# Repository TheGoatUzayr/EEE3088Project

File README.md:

# EEE3088F Design Project – Power Subsystem

This repository contains the development files for our **EEE3088F Design Project**, part of the third-year Electrical & Computer Engineering curriculum at the University of Cape Town.

## 🔧 Project Overview

The broader project is the design and implementation of a **multi-disciplinary embedded system**—a micromouse robot capable of navigating a maze autonomously. The system integrates several subsystems, including:

- 🔋 Power  
- 📡 Sensing  
- 🧠 Processing  

Our team focused on the **power subsystem**, which serves as the electrical backbone of the micromouse.

## ⚡ Power Subsystem Objectives

- Deliver stable and sufficient power to all micromouse subsystems  
- Integrate a safe and efficient **LiPo battery charging** mechanism  
- Include **battery monitoring** to track voltage levels  
- Implement a **low-power idle mode** via a physical switch  
- Ensure seamless integration with the sensing and processing units  

## 📁 Repository Structure

- `README.md` – Project overview and repo guide  
- `simulation/` – Top-level development folder  
  - `pcbdesign1/` – Circuit designs, layouts, and BOM

## 👨‍🔬 Contributors
- Uzayr Ballim – Power subsystem
- Kamil Singh – Power subsystem

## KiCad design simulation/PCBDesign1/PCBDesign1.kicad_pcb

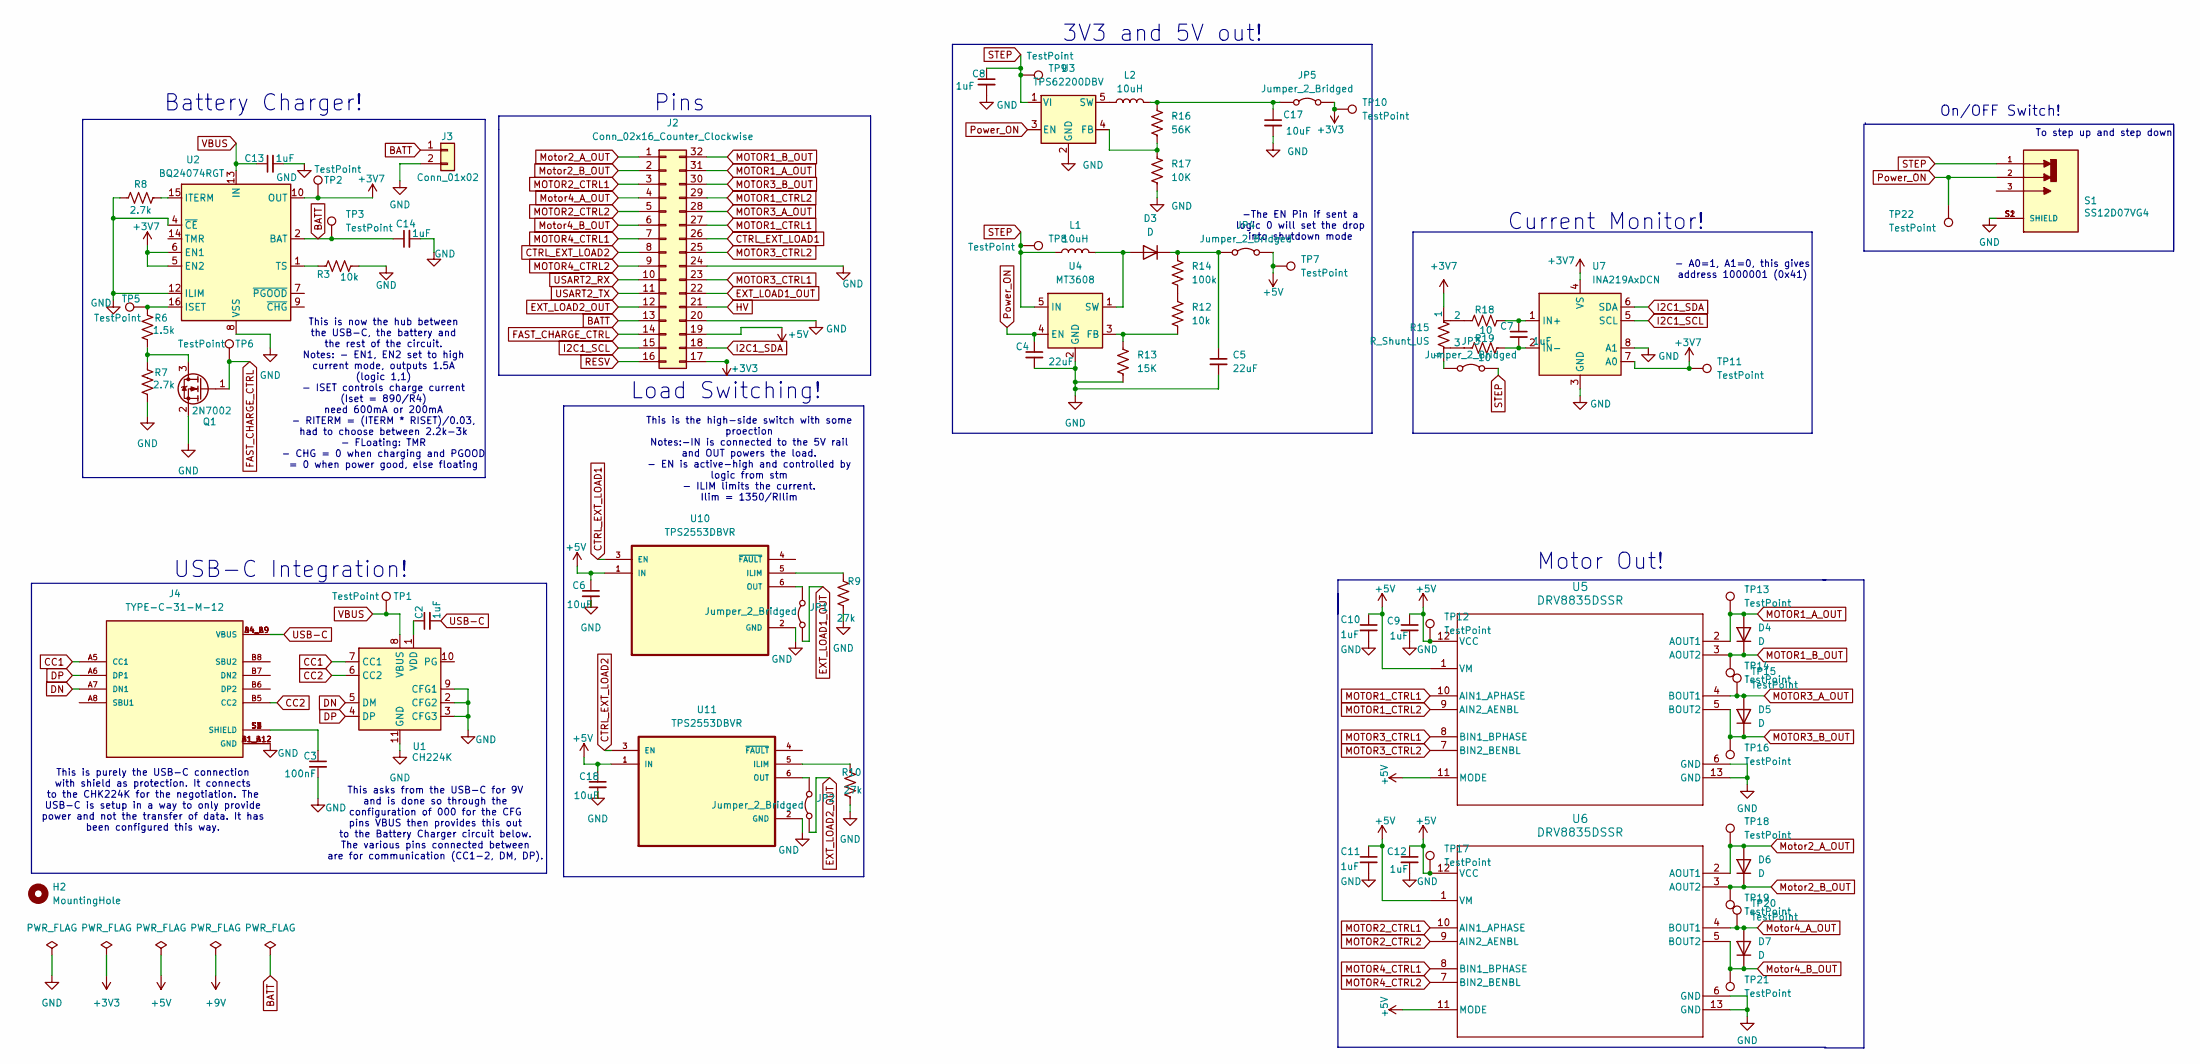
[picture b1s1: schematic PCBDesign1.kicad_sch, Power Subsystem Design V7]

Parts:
C2, C7, C8, C9, C10, C11, C12, C13, C14: 1uF; C_0805_2012Metric_Pad1.18x1.45mm_HandSolder
C3: 100nF; C_0805_2012Metric_Pad1.18x1.45mm_HandSolder
C4, C5: 22uF; C_0805_2012Metric_Pad1.18x1.45mm_HandSolder
C6, C17, C18: 10uF; C_0805_2012Metric_Pad1.18x1.45mm_HandSolder
D3, D4, D5, D6, D7: D; D_2512_6332Metric_Pad1.52x3.35mm_HandSolder
H2: MountingHole; MountingHole_3.2mm_M3_ISO14580_Pad_TopBottom
J2: Conn_02x16_Counter_Clockwise; PinHeader_2x16_P2.54mm_Vertical
J3: Conn_01x02; JST_PH_S2B-PH-K_1x02_P2.00mm_Horizontal
J4: TYPE-C-31-M-12; HRO_TYPE-C-31-M-12; PARTREV 2020.12.08
JP1, JP2, JP3, JP4, JP5: Jumper_2_Bridged; SolderJumper-2_P1.3mm_Bridged_Pad1.0x1.5mm
L1, L2: 10uH; L_Axial_L5.3mm_D2.2mm_P10.16mm_Horizontal_Vishay_IM-1
Q1: 2N7002; SOT-23
R3, R12: 10k; R_0402_1005Metric_Pad0.72x0.64mm_HandSolder
R6: 1.5k; R_0402_1005Metric_Pad0.72x0.64mm_HandSolder
R7, R8: 2.7k; R_0402_1005Metric_Pad0.72x0.64mm_HandSolder
R9, R10: 27k; R_0402_1005Metric_Pad0.72x0.64mm_HandSolder
R13: 15K; R_0402_1005Metric_Pad0.72x0.64mm_HandSolder
R14: 100k; R_0402_1005Metric_Pad0.72x0.64mm_HandSolder
R15: R_Shunt_US; R_Axial_Shunt_L22.2mm_W8.0mm_PS14.30mm_P25.40mm
R16: 56K; R_0402_1005Metric_Pad0.72x0.64mm_HandSolder
R17: 10K; R_0402_1005Metric_Pad0.72x0.64mm_HandSolder
R18, R19: 10; R_0402_1005Metric_Pad0.72x0.64mm_HandSolder
S1: SS12D07VG4; SW_SS12D07VG4; PARTREV 1
TP1, TP2, TP3, TP5, TP6, TP7, TP8, TP9, TP10, TP11, TP12, TP13, TP14, TP15, TP16, TP17, TP18, TP19, TP20, TP21, TP22: TestPoint; TestPoint_Pad_D2.0mm
U1: CH224K; SSOP-10-1EP_3.9x4.9mm_P1mm_EP2.1x3.3mm
U2: BQ24074RGT; VQFN-16-1EP_3x3mm_P0.5mm_EP1.6x1.6mm
U3: TPS62200DBV; SOT-23-5
U4: MT3608; SOT-23-6
U5, U6: DRV8835DSSR; DSS0012A; LCSC C129328
U7: INA219AxDCN; SOT-23-8
U10, U11: TPS2553DBVR; SOT95P280X145-6N; DigiKey_Part_Number 296-32464-2-ND

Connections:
+3V3: J2.17, JP5.2 (B), TP10.1
+3V7: R15.1, TP2.1, TP11.1, U2.5 (EN2), U2.6 (EN1), U2.10 (OUT), U2.11 (OUT), U7.4 (VS), U7.7 (A0)
+5V: C6.1, C9.1, C10.1, C11.1, C12.1, C18.1, J2.19, JP4.2 (B), TP7.1, TP12.1, TP17.1, U5.1 (VM), U5.11 (MODE), U5.12 (VCC), U6.1 (VM), U6.11 (MODE), U6.12 (VCC), U10.1 (IN), U11.1 (IN)
BATT: C14.1, J2.13, J3.1, TP3.1, U2.2 (BAT), U2.3 (BAT)
CC1: J4.A5 (CC1), U1.7 (CC1)
CC2: J4.B5 (CC2), U1.6 (CC2)
CTRL_EXT_LOAD1: J2.26, U10.3 (EN)
CTRL_EXT_LOAD2: J2.8, U11.3 (EN)
DN: J4.A7 (DN1), U1.5 (DM)
DP: J4.A6 (DP1), U1.4 (DP)
EXT_LOAD1_OUT: J2.22, JP1.1 (A)
EXT_LOAD2_OUT: J2.12, JP2.1 (A)
FAST_CHARGE_CTRL: J2.14, Q1.1 (G), TP6.1
GND: C3.2, C4.2, C5.2, C6.2, C8.2, C9.2, C10.2, C11.2, C12.2, C13.2, C14.2, C17.2, C18.2, J2.20, J2.24, J3.2, J4.A1_B12 (GND), J4.B1_A12 (GND), Q1.2 (S), R3.1, R7.1, R8.2, R9.1, R10.1, R13.2, R17.2, S1.S1 (SHIELD), S1.S2 (SHIELD), U1.2 (CFG2), U1.3 (CFG3), U1.9 (CFG1), U1.11 (GND), U2.4 (~CE), U2.8 (VSS), U2.12 (ILIM), U2.17 (VSS), U3.2 (GND), U4.2 (GND), U5.6 (GND), U5.13 (GND), U6.6 (GND), U6.13 (GND), U7.3 (GND), U7.8 (A1), U10.2 (GND), U11.2 (GND)
HV: J2.21
I2C1_SCL: J2.15, U7.5 (SCL)
I2C1_SDA: J2.18, U7.6 (SDA)
MOTOR1_A_OUT: D4.2 (A), J2.31, TP13.1, U5.2 (AOUT1)
MOTOR1_B_OUT: D4.1 (K), J2.32, TP14.1, U5.3 (AOUT2)
MOTOR1_CTRL1: J2.27, U5.10 (AIN1_APHASE)
MOTOR1_CTRL2: J2.29, U5.9 (AIN2_AENBL)
MOTOR2_CTRL1: J2.3, U6.10 (AIN1_APHASE)
MOTOR2_CTRL2: J2.5, U6.9 (AIN2_AENBL)
MOTOR3_A_OUT: D5.2 (A), J2.28, TP15.1, U5.4 (BOUT1)
MOTOR3_B_OUT: D5.1 (K), J2.30, TP16.1, U5.5 (BOUT2)
MOTOR3_CTRL1: J2.23, U5.8 (BIN1_BPHASE)
MOTOR3_CTRL2: J2.25, U5.7 (BIN2_BENBL)
MOTOR4_CTRL1: J2.7, U6.8 (BIN1_BPHASE)
MOTOR4_CTRL2: J2.9, U6.7 (BIN2_BENBL)
Motor2_A_OUT: D6.2 (A), J2.1, TP18.1, U6.2 (AOUT1)
Motor2_B_OUT: D6.1 (K), J2.2, TP19.1, U6.3 (AOUT2)
Motor4_A_OUT: D7.2 (A), J2.4, TP20.1, U6.4 (BOUT1)
Motor4_B_OUT: D7.1 (K), J2.6, TP21.1, U6.5 (BOUT2)
unnamed: C3.1, J4.S1 (SHIELD), J4.S2 (SHIELD), J4.S3 (SHIELD), J4.S4 (SHIELD)
unnamed: D3.2 (A), L1.2, U4.1 (SW)
unnamed: C5.1, D3.1 (K), JP4.1 (A), R14.1
unnamed: JP1.2 (B), U10.6 (OUT)
unnamed: JP2.2 (B), U11.6 (OUT)
unnamed: JP3.1 (A), R15.4
unnamed: C17.1, JP5.1 (A), L2.2, R16.1
unnamed: Q1.3 (D), R6.1, R7.2
unnamed: R12.1, R14.2
unnamed: R15.2, R18.1
unnamed: R15.3, R19.1
unnamed: C2.1, U1.1 (VDD)
unnamed: R6.2, TP5.1, U2.16 (ISET)
unnamed: R8.1, U2.15 (ITERM)
unnamed: R3.2, U2.1 (TS)
unnamed: R16.2, R17.1, U3.4 (FB)
unnamed: L2.1, U3.5 (SW)
unnamed: R12.2, R13.1, U4.3 (FB)
unnamed: C7.1, R18.2, U7.1 (IN+)
unnamed: C7.2, R19.2, U7.2 (IN-)
unnamed: R9.2, U10.5 (ILIM)
unnamed: R10.2, U11.5 (ILIM)
Power_ON: C4.1, S1.2, TP22.1, U3.3 (EN), U4.4 (EN)
RESV: J2.16
STEP: C8.1, JP3.2 (B), L1.1, S1.1, TP8.1, TP9.1, U3.1 (VI), U4.5 (IN)
USART2_RX: J2.10
USART2_TX: J2.11
USB-C: C2.2, J4.A4_B9 (VBUS), J4.B4_A9 (VBUS)
VBUS: C13.1, TP1.1, U1.8 (VBUS), U2.13 (IN)

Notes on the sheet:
To step up and step down
- A0=1, A1=0, this gives address 1000001 (0x41)
This is purely the USB-C connection with shield as protection. It connects to the CHK224K for the negotiation. The USB-C is setup in a way to only provide power and not the transfer of data. It has been configured this way.
Current Monitor!
Motor Out!
USB-C Integration!
This asks from the USB-C for 9V and is done so through the configuration of 000 for the CFG pins VBUS then provides this out to the Battery Charger circuit below. The various pins connected between are for communication (CC1-2, DM, DP).
This is now the hub between the USB-C, the battery and the rest of the circuit. Notes: - EN1, EN2 set to high current mode, outputs 1.5A (logic 1,1) - ISET controls charge current (Iset = 890/R4) need 600mA or 200mA - RITERM = (ITERM * RISET)/0.03, had to choose between 2.2k-3k - FLoating: TMR - CH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
-The EN Pin if sent a logic 0 will set the drop into shutdown mode
Pins
Battery Charger!
This is the high-side switch with some proection Notes:-IN is connected to the 5V rail and OUT powers the load. - EN is active-high and controlled by logic from stm - ILIM limits the current. Ilim = 1350/RIlim
On/OFF Switch!
3V3 and 5V out!
Load Switching!

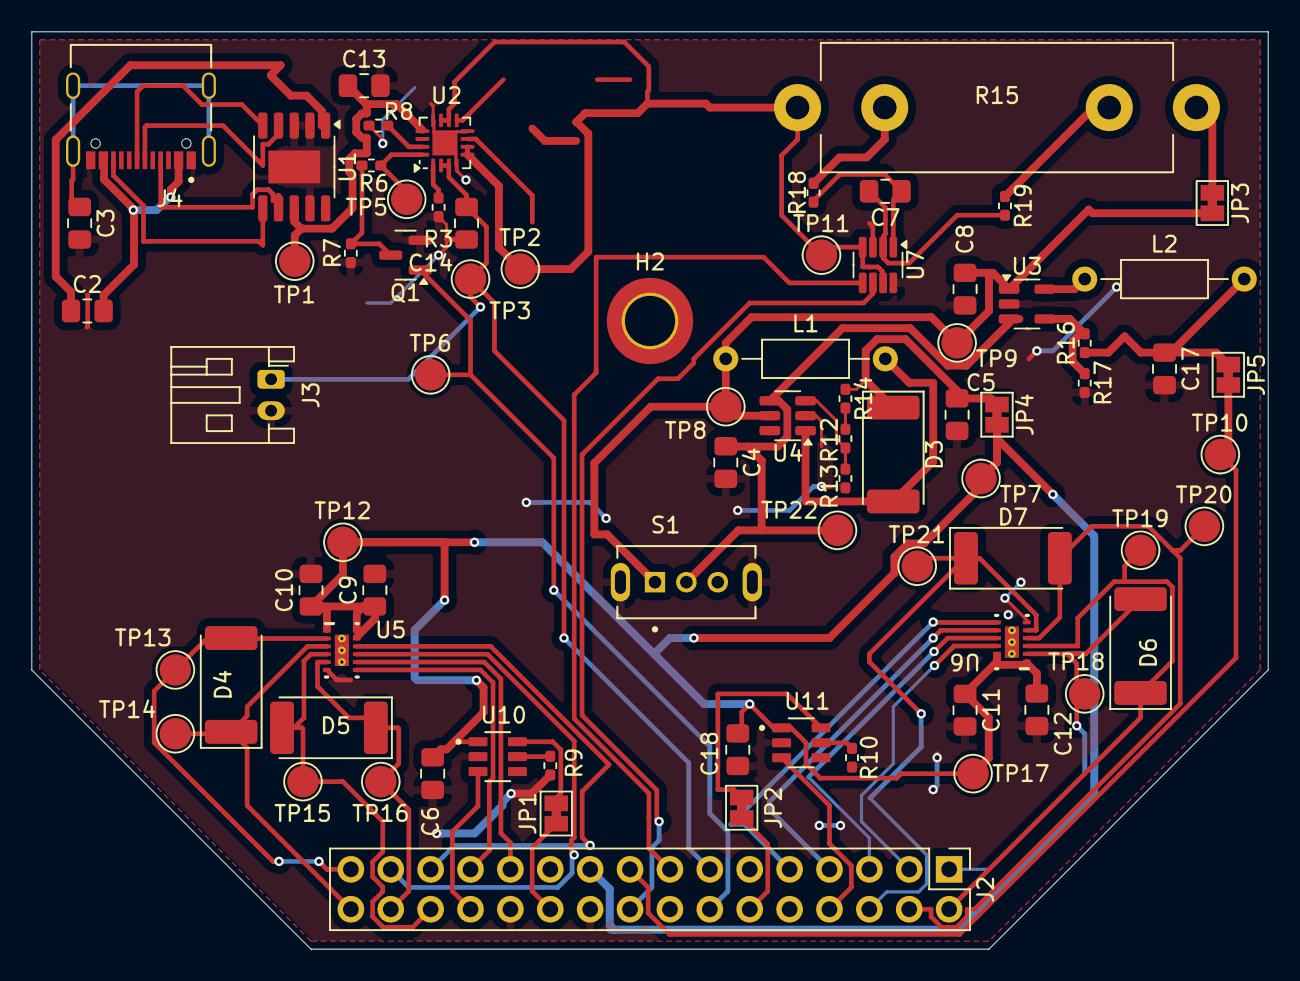
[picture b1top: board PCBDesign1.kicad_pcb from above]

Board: 2 copper layers, 78.7 x 58.4 mm, 77 parts (0 on the bottom side), 58 nets.

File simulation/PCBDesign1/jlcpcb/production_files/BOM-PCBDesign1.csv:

Comment,Designator,Footprint,LCSC,Quantity
10uH,"L1,L2",L_Axial_L5.3mm_D2.2mm_P10.16mm_Horizontal_Vishay_IM-1,C1046,2
DRV8835DSSR,"U5,U6",DSS0012A,C129328,2
10uF,"C17,C18,C6",C_0805_2012Metric_Pad1.18x1.45mm_HandSolder,C15850,3
TYPE-C-31-M-12,J4,HRO_TYPE-C-31-M-12,C165948,1
2.7k,"R7,R8",R_0402_1005Metric_Pad0.72x0.64mm_HandSolder,C17530,2
27k,"R10,R9",R_0402_1005Metric_Pad0.72x0.64mm_HandSolder,C17593,2
SS12D07VG4,S1,SW_SS12D07VG4,C22435633,1
56K,R16,R_0402_1005Metric_Pad0.72x0.64mm_HandSolder,C23206,1
10,"R18,R19",R_0402_1005Metric_Pad0.72x0.64mm_HandSolder,C25077,2
100k,R14,R_0402_1005Metric_Pad0.72x0.64mm_HandSolder,C25741,1
10k,"R12,R17,R3",R_0402_1005Metric_Pad0.72x0.64mm_HandSolder,C25744,3
15K,R13,R_0402_1005Metric_Pad0.72x0.64mm_HandSolder,C25756,1
1.5k,R6,R_0402_1005Metric_Pad0.72x0.64mm_HandSolder,C25867,1
100nF,C3,C_0805_2012Metric_Pad1.18x1.45mm_HandSolder,C28233,1
1uF,"C10,C11,C12,C13,C14,C2,C7,C8,C9",C_0805_2012Metric_Pad1.18x1.45mm_HandSolder,C28323,9
22uF,"C4,C5",C_0805_2012Metric_Pad1.18x1.45mm_HandSolder,C45783,2
BQ24074RGT,U2,VQFN-16-1EP_3x3mm_P0.5mm_EP1.6x1.6mm,C54313,1
TPS2553DBVR,"U10,U11",SOT95P280X145-6N,C55266,2
R_Shunt_US,R15,R_Axial_Shunt_L22.2mm_W8.0mm_PS14.30mm_P25.40mm,C7467250,1
MT3608,U4,SOT-23-6,C84817,1
2N7002,Q1,SOT-23,C8545,1
INA219AxDCN,U7,SOT-23-8,C87469,1
TPS62200DBV,U3,SOT-23-5,C9048,1
D,"D3,D4,D5,D6,D7",D_2512_6332Metric_Pad1.52x3.35mm_HandSolder,C95872,5
CH224K,U1,SSOP-10-1EP_3.9x4.9mm_P1mm_EP2.1x3.3mm,C970725,1

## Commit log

2025-03-28 version 23
2025-03-28 Add files via upload
    uploaded version with all components assigned on JLCPCB
2025-05-09 Restructured repo: keep README at root and add simulation/pcbdesign1
